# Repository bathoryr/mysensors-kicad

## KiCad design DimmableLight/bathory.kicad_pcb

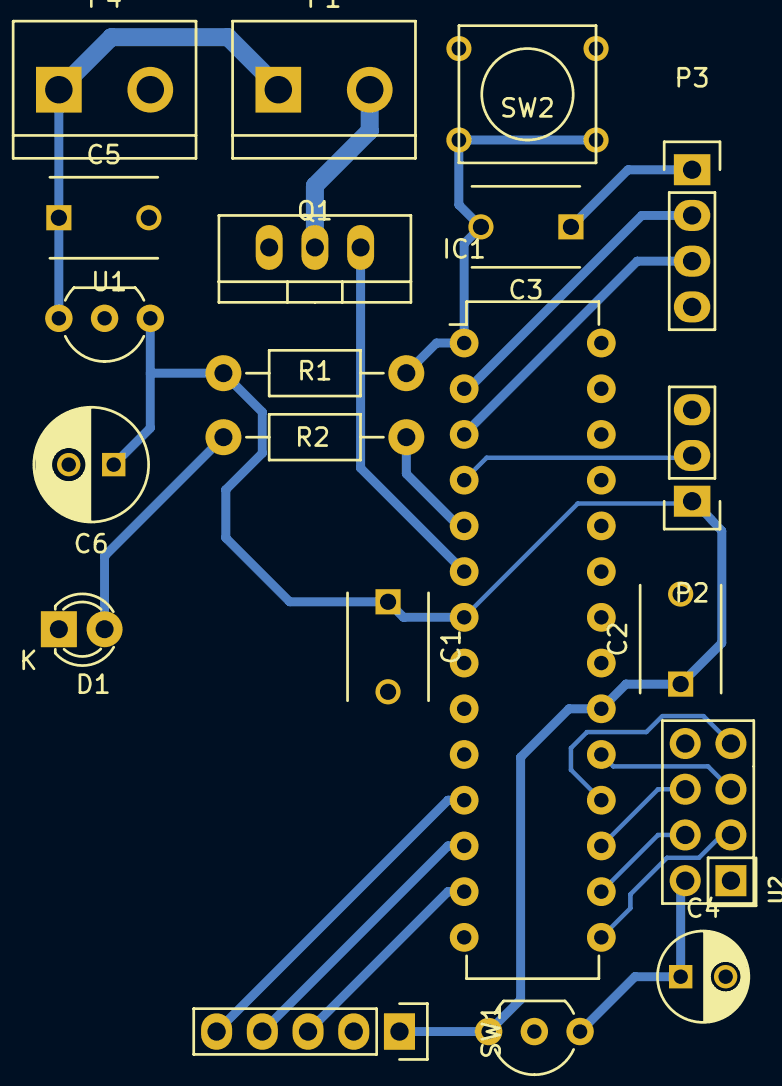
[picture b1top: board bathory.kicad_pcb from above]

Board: 2 copper layers, 20 parts (0 on the bottom side), 21 nets.

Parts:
C1, C2, C3, C5: 100n; C_Disc_D6_P5
C4: 4M7; C_Radial_D5_L11_P2.5
C6: 10M; C_Radial_D6.3_L11.2_P2.5
D1: Green LED; LED-3MM
IC1: ATMEGA328P-P; DIP-28_W7.62mm
P1: LED conn; bornier2
P2: RC control; Pin_Header_Straight_1x03
P3: FTDI; Pin_Header_Straight_1x04
P4: INPUT VCC; bornier2
Q1: IRLZ44; TO-220_Neutral123_Vertical
R1: 10K; Resistor_Horizontal_RM10mm
R2: 470; Resistor_Horizontal_RM10mm
SW1: Coded_Switch; Pin_Header_Straight_1x05
SW2: Reset; SW_PUSH_SMALL
U1: LE50; TO-92_Inline_Wide
U2: NRF24L01
U3: LE33; TO-92_Inline_Wide

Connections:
+5V: C1.1, C2.1, C6.1, IC1.7, IC1.20, P2.1, R1.1, SW1.1, U1.1, U3.3
/CE: IC1.15, U2.3
/CLK: IC1.11, SW1.5
/CSN: IC1.16, U2.4
/DT: IC1.12, SW1.4
/MISO: IC1.18, U2.7
/MOSI: IC1.17, U2.6
/SCK: IC1.19, U2.5
/SW: IC1.13, SW1.3
GND: C1.2, C2.2, C4.2, C5.2, C6.2, D1.1, IC1.8, IC1.22, P2.3, P3.4, P4.2, Q1.3, SW1.2, SW2.2, U1.2, U2.1, U3.2
unnamed: C3.1, P3.1
unnamed: C3.2, IC1.1, R1.2, SW2.1
unnamed: C4.1, U2.2, U3.1
unnamed: D1.2, R2.1
unnamed: IC1.2, P3.2
unnamed: IC1.3, P3.3
unnamed: IC1.4, P2.2
unnamed: IC1.5, R2.2
unnamed: IC1.6, Q1.1
unnamed: P1.2, Q1.2
VCC: C5.1, P1.1, P4.1, U1.3

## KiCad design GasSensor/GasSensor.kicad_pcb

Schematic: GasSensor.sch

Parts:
C1, C9: 10n; C_Disc_D6_P5
C2: 1u; C_Disc_D6_P5
C3, C4, C8: 100n; C_Disc_D6_P5
C5, C6: 22p; C_Disc_D6_P5
C7: 10u; C_Radial_D7.5_L11.2_P2.5
IC1: ATMEGA328P-P; DIP-28_W7.62mm
P1: FTDI; Pin_Header_Straight_1x04
P2: Reed sensor; Pin_Header_Straight_1x02
P3: Battery; Pin_Header_Straight_1x02
R1: 1M; Resistor_Horizontal_RM10mm
R2: 270k; Resistor_Horizontal_RM10mm
R3, R4: 10k; Resistor_Horizontal_RM10mm
SW1: Reset btn; SW_PUSH_6mm_h13mm
U1: MCP1703A-3302/MB; TO-92_Molded_Narrow_Oval
U2: 74HC14; DIP-14_W7.62mm
U3: NRF24L01
Y1: 8MHz; Crystal_HC49-U_Vertical

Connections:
+3V3: C3.1, C4.1, C7.1, IC1.7 (VCC), IC1.20 (AVCC), R3.1, R4.1, U1.3, U2.14 (VCC), U3.2 (VCC)
/CE: IC1.15 ((PCINT1/OC1A)PB1), U3.3 (CE)
/CSN: IC1.16 ((PCINT2/OC1B/~SS~)PB2), U3.4 (CSN)
/MISO: IC1.18 ((PCINT4/MISO)PB4), U3.7 (MISO)
/MOSI: IC1.17 ((PCINT3/OC2A/MOSI)PB3), U3.6 (MOSI)
/RST: C8.2, P1.1
/RX: IC1.2 ((PCINT16/RXD)PD0), P1.2
/SCK: IC1.19 ((PCINT5/SCK)PB5), U3.5 (SCK)
/TX: IC1.3 ((PCINT17/TXD)PD1), P1.3
/VDET: C1.1, IC1.23 ((PCINT8/ADC0)PC0), R1.2, R2.1
GND: C1.2, C2.2, C3.2, C4.2, C5.2, C6.2, C7.2, C9.2, IC1.8 (GND), IC1.22 (GND), P1.4, P2.2, P3.1, R2.2, SW1.2, U1.1, U2.7 (GND), U3.1 (GND)
unnamed: C2.1, P3.2, R1.1, U1.2
unnamed: C5.1, IC1.10 ((PCINT7/XTAL2/TOSC2)PB7), Y1.1
unnamed: C6.1, IC1.9 ((PCINT6/XTAL1/TOSC1)PB6), Y1.2
unnamed: C8.1, IC1.1 ((PCINT14/~RESET~)PC6), R3.2, SW1.1
unnamed: C9.1, P2.1, R4.2, U2.1
unnamed: IC1.4 ((PCINT18/INT0)PD2), U2.2

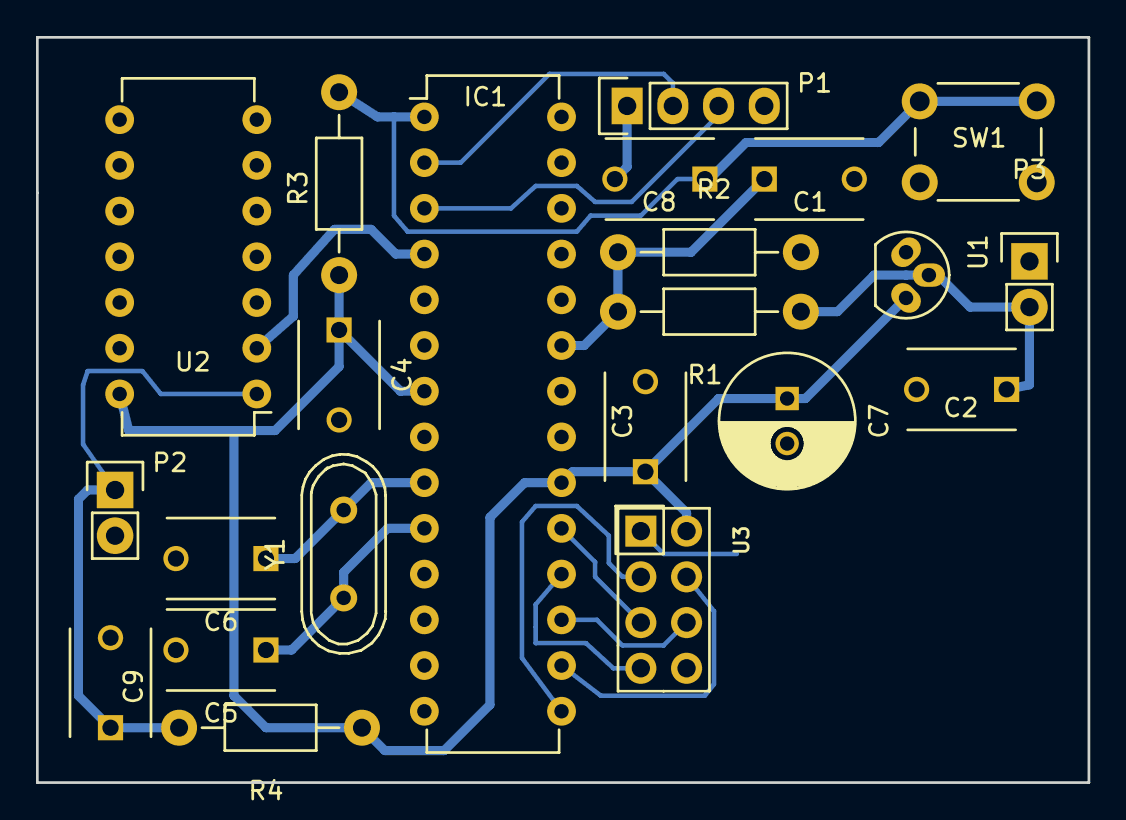
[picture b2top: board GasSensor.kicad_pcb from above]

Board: 2 copper layers, 58.4 x 41.4 mm, 22 parts (0 on the bottom side), 17 nets.

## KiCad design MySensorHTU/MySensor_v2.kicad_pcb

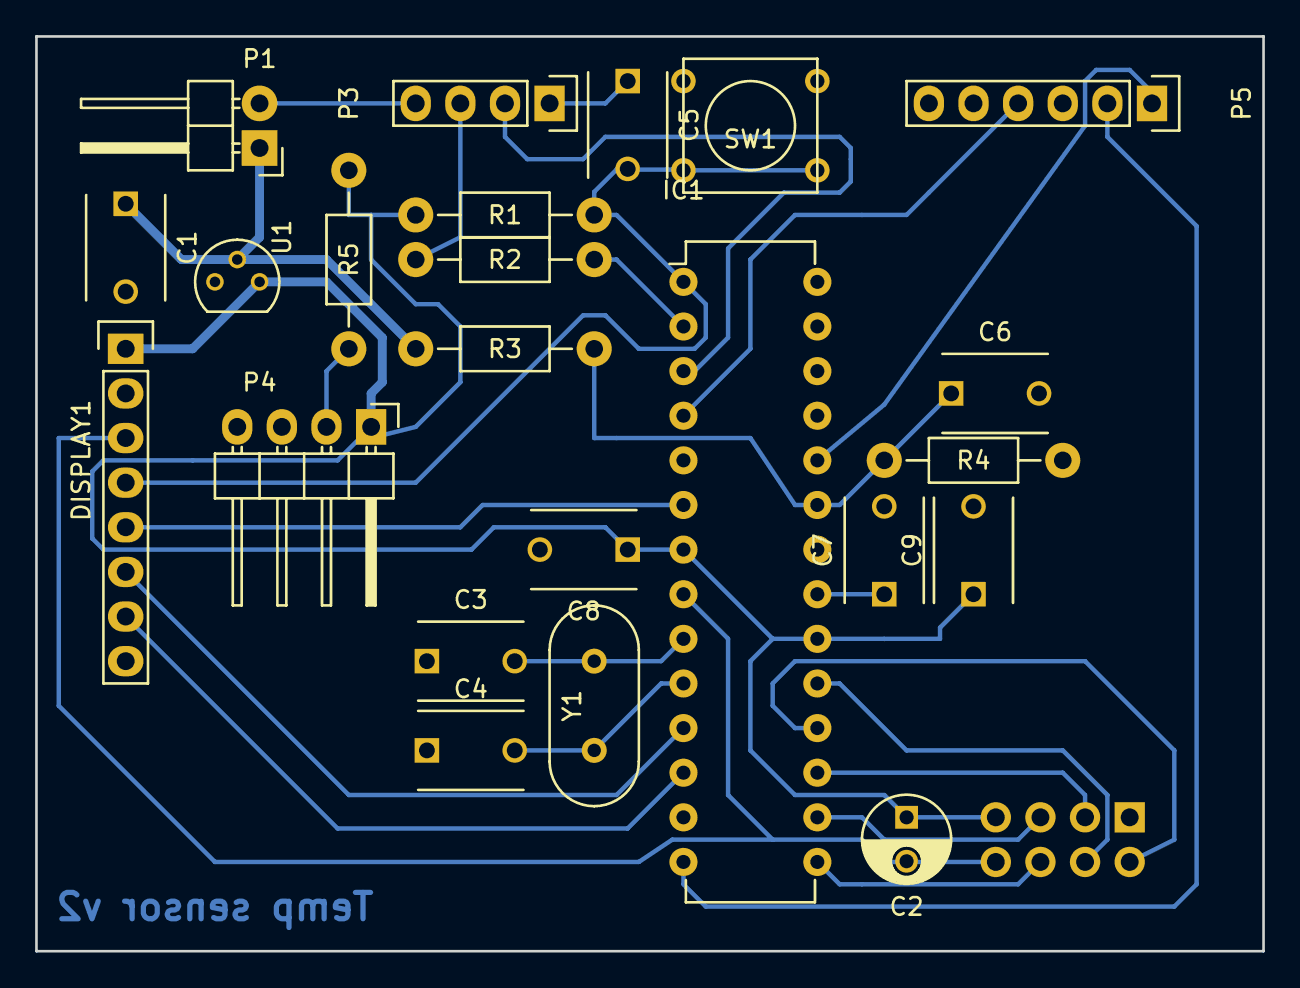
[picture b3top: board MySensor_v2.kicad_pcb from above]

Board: 2 copper layers, 69.8 x 52.1 mm, 24 parts (1 on the bottom side), 25 nets.

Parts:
C1, C5, C6, C7, C8, C9: 100n; C_Disc_D6_P5
C2: 10u; C_Radial_D5_L6_P2.5
C3, C4: 22p; C_Disc_D6_P5
DISPLAY1: PCD8544; Socket_Strip_Straight_1x08
IC1: ATMEGA328P-P; DIP-28_W7.62mm
P1: Batt; Pin_Header_Angled_1x02
P2: NRF24L01+; Socket_Strip_Straight_2x04
P3: FTDI; Pin_Header_Straight_1x04
P4: DHT22; Pin_Header_Angled_1x04
P5: PINOUT; Pin_Header_Straight_1x06
R1, R2, R5: 10k; Resistor_Horizontal_RM10mm
R3: 1M; Resistor_Horizontal_RM10mm
R4: 270K; Resistor_Horizontal_RM10mm
SW1: RESET BTN; SW_PUSH_SMALL
U1: MCP1702; TO-92_Molded_Narrow
Y1: 16M; HC-49V

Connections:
+3V3: C2.1, C8.1, C9.1, DISPLAY1.1, IC1.7, IC1.20, P2.7, P4.1, P5.5, R1.1, R5.2, U1.3
/A0: C6.1, IC1.23, R3.2, R4.1
/A1: IC1.24, P5.1
/CE: IC1.15, P2.6
/CS: IC1.16, P2.5
/D2: IC1.4, P5.4
/D3: IC1.5, P5.3
/D8: IC1.14, P5.2
/D/C: DISPLAY1.5, IC1.6
/DIN: DISPLAY1.6, IC1.11
/MISO: IC1.18, P2.2
/MOSI: IC1.17, P2.3
/RESET: C5.1, P3.1
/RST: C5.2, DISPLAY1.4, IC1.1, R1.2, SW1.1
/RX: IC1.3, P3.2
/SCK: IC1.19, P2.4
/SCLK: DISPLAY1.7, IC1.12
/TX: P3.3, R2.1
GND: C1.2, C2.2, C3.1, C4.1, C6.2, C7.2, C8.2, C9.2, DISPLAY1.2, DISPLAY1.3, IC1.8, IC1.22, P1.2, P2.8, P3.4, P4.4, P5.6, R4.2, SW1.2, U1.1
unnamed: C1.1, P1.1, R3.1, U1.2
unnamed: C3.2, IC1.9, Y1.1
unnamed: C4.2, IC1.10, Y1.2
unnamed: C7.1, IC1.21
unnamed: IC1.2, R2.2
unnamed: IC1.13, P4.2, R5.1

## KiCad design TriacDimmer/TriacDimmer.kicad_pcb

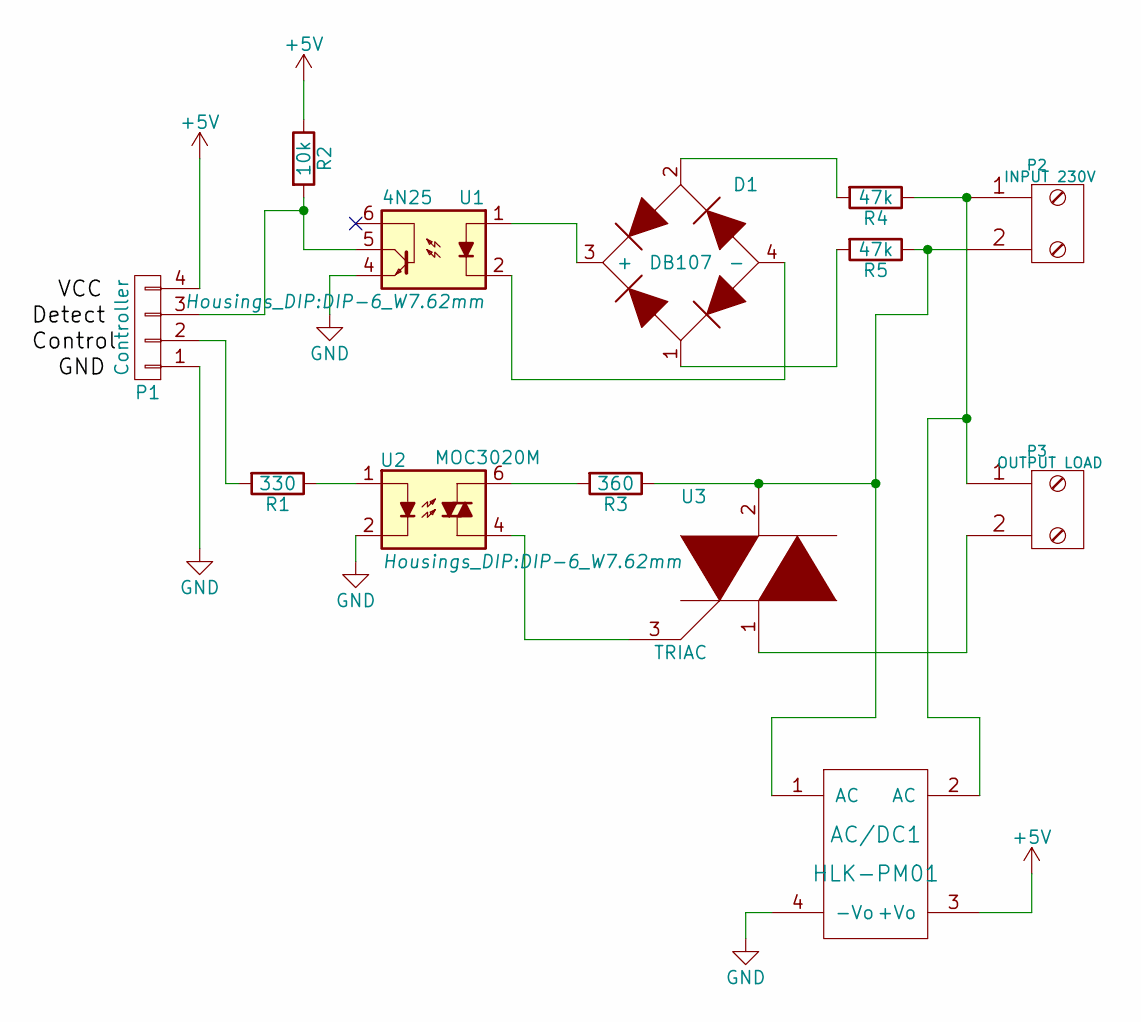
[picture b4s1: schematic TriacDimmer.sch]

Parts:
AC/DC1: HLK-PM01
D1: DB107; DIP-4-6_W7.62mm
P1: Controller; Pin_Header_Straight_1x04
P2: INPUT 230V; bornier2
P3: OUTPUT LOAD; bornier2
R1: 330; Resistor_Vertical_RM5mm
R2: 10k; Resistor_Horizontal_RM10mm
R3: 360; Resistor_Horizontal_RM10mm
R4, R5: 47k; Resistor_Horizontal_RM10mm
U1: 4N25; DIP-6_W7.62mm
U2: MOC3020M; DIP-6_W7.62mm
U3: TRIAC; TO-220_Neutral123_Vertical

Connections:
+5V: AC/DC1.3 (+Vo), P1.4, R2.1
GND: AC/DC1.4 (-Vo), P1.1, U1.4, U2.2
unnamed: AC/DC1.1 (AC), P2.2, R3.1, R5.1, U3.2
unnamed: AC/DC1.2 (AC), P2.1, P3.1, R4.1
unnamed: D1.1, R5.2
unnamed: D1.2, R4.2
unnamed: D1.3 (+), U1.1
unnamed: D1.4 (-), U1.2
unnamed: P1.2, R1.2
unnamed: P1.3, R2.2, U1.5
unnamed: P3.2, U3.1
unnamed: R1.1, U2.1
unnamed: R3.2, U2.6
unnamed: U2.4, U3.3

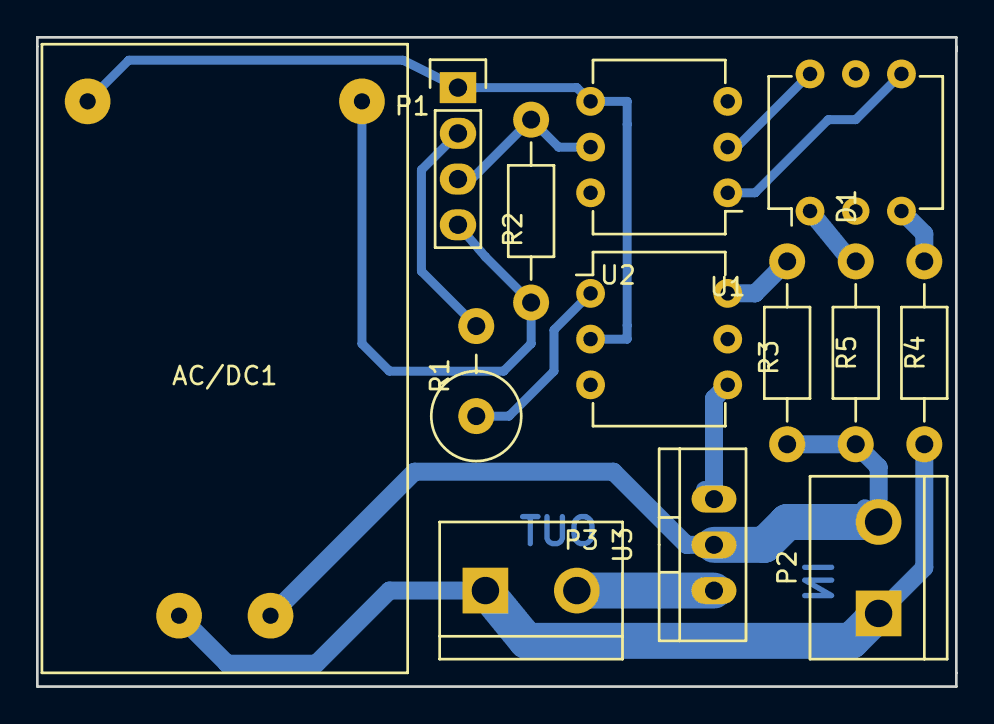
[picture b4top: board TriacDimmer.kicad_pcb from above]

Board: 2 copper layers, 51.1 x 36.1 mm, 13 parts (0 on the bottom side), 14 nets.
